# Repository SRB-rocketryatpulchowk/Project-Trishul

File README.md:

# Project-Trishul
This documentation presents the development of the data collection and parachute ejection system by Team SRB, which aimed to achieve an apogee of 3000 meters.

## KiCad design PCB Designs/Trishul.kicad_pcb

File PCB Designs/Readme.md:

This folder contains the final version of pcb designs, schematics. And also the libraries and footprints of components.
This folder contains a total of 3 different PCB Designs: 
1. Main PCB (Teensy Based PCB; acts as a main flight computer)
2. TRISHUL NANO( Arduino Nano based PCB; acts as a backup flight computer, whose sole role is to eject the parachute with timer based redundancy too)
3. LORA Receiver(This is the ground based reciever module for recieving live telemetry data)

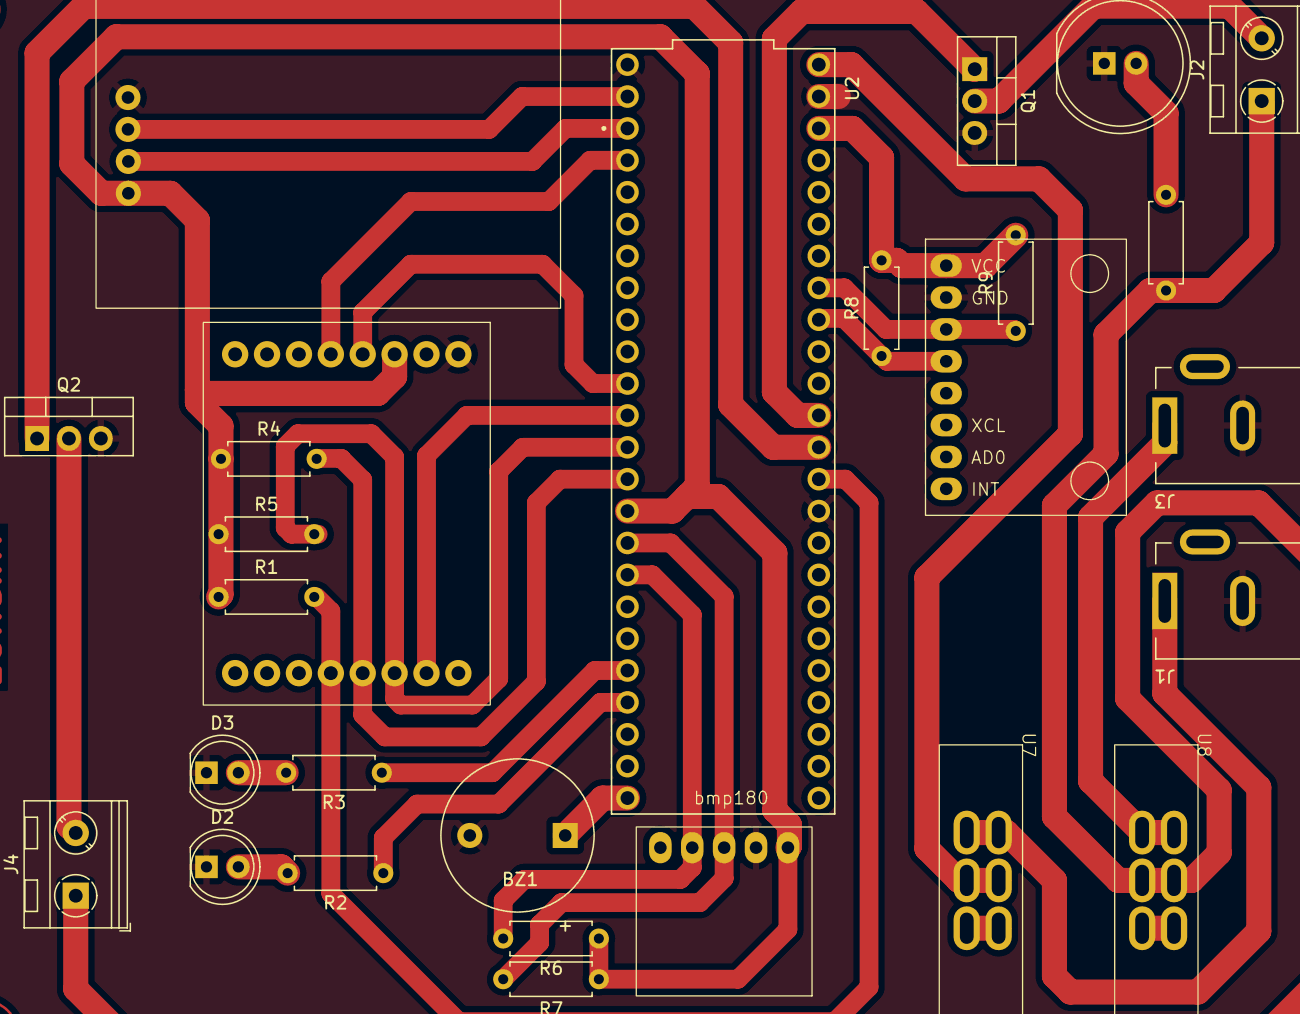
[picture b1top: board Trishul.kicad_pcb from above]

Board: 2 copper layers, 27 parts (0 on the bottom side), 30 nets.

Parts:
BZ1: Buzzer; Buzzer_12x9.5RM7.6
D1: LED; LED_D10.0mm
D2, D3: LED; LED_D5.0mm
J1, J3: Barrel_Jack_MountingPin; BarrelJack_Kycon_KLDX-0202-xC_Horizontal
J2, J4: Screw_Terminal_01x02; TerminalBlock_RND_205-00045_1x02_P5.00mm_Horizontal
Q1: IRFZ44N; TO-220-3_Vertical
Q2: IRF540N; TO-220-3_Vertical
R1, R2, R3, R4, R5, R6, R7, R8, R9, R10: R; R_Axial_DIN0207_L6.3mm_D2.5mm_P7.62mm_Horizontal
U2: DEV-16771; MODULE_DEV-16771
U3: GPS
U4: BMP180
U5: mpu6050
U6: LoRa-02
U7, U8: SLIDER PIN

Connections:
GND: BZ1.2 (-), D1.1 (K), D2.1 (K), D3.1 (K), J1.2, J3.2, Q1.3, Q2.3 (S), U2.GND1 (GND), U2.GND2 (GND), U2.GND3 (GND), U3.4 (GND), U4.2 (GND), U5.2 (GND), U6.1 (GND)
unnamed: BZ1.1 (+), U2.32 (OUT1B)
unnamed: D1.2 (A), R10.2
unnamed: D2.2 (A), R2.2
unnamed: D3.2 (A), R3.2
unnamed: J1.1, U7.1, U7.2
unnamed: J2.1, J4.1, R10.1, U8.5, U8.6
unnamed: J2.2, Q1.2
unnamed: J3.1, U8.1, U8.2
unnamed: J4.2, Q2.2 (D)
unnamed: Q2.1 (G), U2.14 (A0)
unnamed: Q1.1, U2.15 (A1)
unnamed: R8.1, U2.18 (A4), U5.4 (SDA)
unnamed: R9.1, U2.19 (A5), U5.3 (SCL)
unnamed: R7.2, U2.24 (A10), U4.3 (SCL)
unnamed: R6.2, U2.25 (A11), U4.4 (SDA)
unnamed: U2.10 (CS1), U6.10 (NSS)
unnamed: R4.2, U2.12 (MISO), U6.12 (MISO)
unnamed: R5.2, U2.11 (MOSI), U6.11 (MOSI)
unnamed: U2.9 (OUT1C), U6.4 (RST)
unnamed: U2.2 (OUT2), U6.5 (DIOO)
unnamed: U2.VIN, U7.5, U7.6
unnamed: U2.0 (RX1), U3.3 (TX)
unnamed: R3.1, U2.28 (RX7)
unnamed: R1.2, U2.13 (SCK), U6.13 (SCK)
unnamed: U2.1 (TX1), U3.2 (RX)
unnamed: R2.1, U2.29 (TX7)
unnamed: R1.1, R4.1, R5.1, R6.1, R7.1, R8.2, R9.2, U2.3.3V_1 (3.3V), U2.3.3V_2 (3.3V), U3.1 (Vcc), U4.1 (Vcc), U5.1 (Vcc), U6.3 (3.3V)
unnamed: U7.3, U7.4
unnamed: U8.3, U8.4

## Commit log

2025-04-28 Added PROJECT-TRISHUL complete folder with codes and libraries
2025-04-28 Added README for customized libraries
2025-04-28 Added README for test codes
2025-04-28 Create PCB Designs Kicad
2025-04-28 Added full Project-Trishul codebase
2025-04-30 Add README.md under 'Problems faced and solutions implemented' folder
